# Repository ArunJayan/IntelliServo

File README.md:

IntelliServo
===================================================================

##Overview
IntelliServo is a project aiming to transform regular hobby servos into intelligent ones by replacing their original boards. 
By doing so the servo has upgraded capabilities, such as being able to read its position, temperature and current consumption. 
Multiple servos can now be daisy-chained and controlled over I2C from a microcontroller, or over USB from a computer.

Each board features an LPC11U24 microcontroller, a DRV8837 motor driver, a TMP36 temperature sensor and a PCA9508 I2C repeater.
Each servo is unique, and so the list of compatible servos will expand with the community, so don't hesitate to add your servo!

<div style="width: 100%; display: table;">
<div style="display: table-row">

<div align="center" style="display: table-cell;"><p align="center"><a href="https://youtu.be/W2uScJmLD4c" target="_blank">Master/Slave configuration</a></p></div>

<div align="center" style="display: table-cell;">
<p align="center"><a href="https://youtu.be/FjYgxcrhwy4" target="_blank">Touch detection</a></p>
</div>

</div>
</div>

##Connections
V_BAT: Main power line, energizes the motor and all the servo's ICs. Works between 5 and 12 volts.
V_I2C: Voltage reference for the I2C bus and powers components on the auxiliary bus. Must be 3.3V or 5V.

The servo has different connector groups:
* Main bus (5 lines): It is used to power and control the servos in daisy-chain configuration, attaching each one's A side to the previous' B side.
* Auxiliary bus (4 lines): Its function is to provide an extra link to the I2C bus, to allow other devices to be used at the same time.
* Power bus (2 lines): The main bus can be powered from the power bus on any servo, or from the last servo's main bus V_BAT and GND.
* Micro USB: Used both to upload the firmware to the board as to use it to control the servo directly from the PC, without involving other microcontrollers.

##Installing Firmware
The board runs the firmware included in the Software/Firmware section. It is written in C++ and uses Mbed, to upload it connect the board over USB and then power it using the V_BAT and GND lines while pressing the button. 

To compile it use the "mBuino" Mbed platform, which uses the smaller LPC11U24FHI33/301 model instead of the larger LPC11U24FBD64/401 model normally used in other boards. This is important because the EEPROM memory maps are different between both and the board won't be able to access the EEPROM until the right platform is chosen.

##Library
The servos are controlled over I2C, but to simplify their use an arduino library with all the relevant functions and some example sketches are included as well. 
To install it simply copy it to the "sketchbook/libraries/" folder. 

##Specifications
V_BAT:&nbsp;&nbsp;&nbsp;&nbsp;&nbsp;5V-12V
V_I2C:&nbsp;&nbsp;&nbsp;&nbsp;&nbsp;&nbsp;&nbsp;3.3V/5V
I_Servo:&nbsp;&nbsp;&nbsp;&nbsp;1.8A max
I_Line:&nbsp;&nbsp;&nbsp;&nbsp;&nbsp;&nbsp;&nbsp;5A max (60mil trace)

##Contributing
This project is open-source and as so everyone is welcome to contribute. The most useful way of doing so is perhaps by expanding the list of compatible servos, by finding the moving range in degrees and PID parameters specific for each servo.

To do so add the servo to the IntelliServoConfig.h file as below

```cpp
//Added by username
#ifdef NAME_OF_SERVO
    float maxAngle=XXX;
    float Kp=XXX, Kd=XXX, Ki=XXX;
#endif
```
and to the IntelliServoMain.cpp file
```cpp
//#define NAME_OF_SERVO
```

##License
This project is licensed under Creative Commons Attribution-ShareAlike 4.0 International (CC BY-SA 4.0)

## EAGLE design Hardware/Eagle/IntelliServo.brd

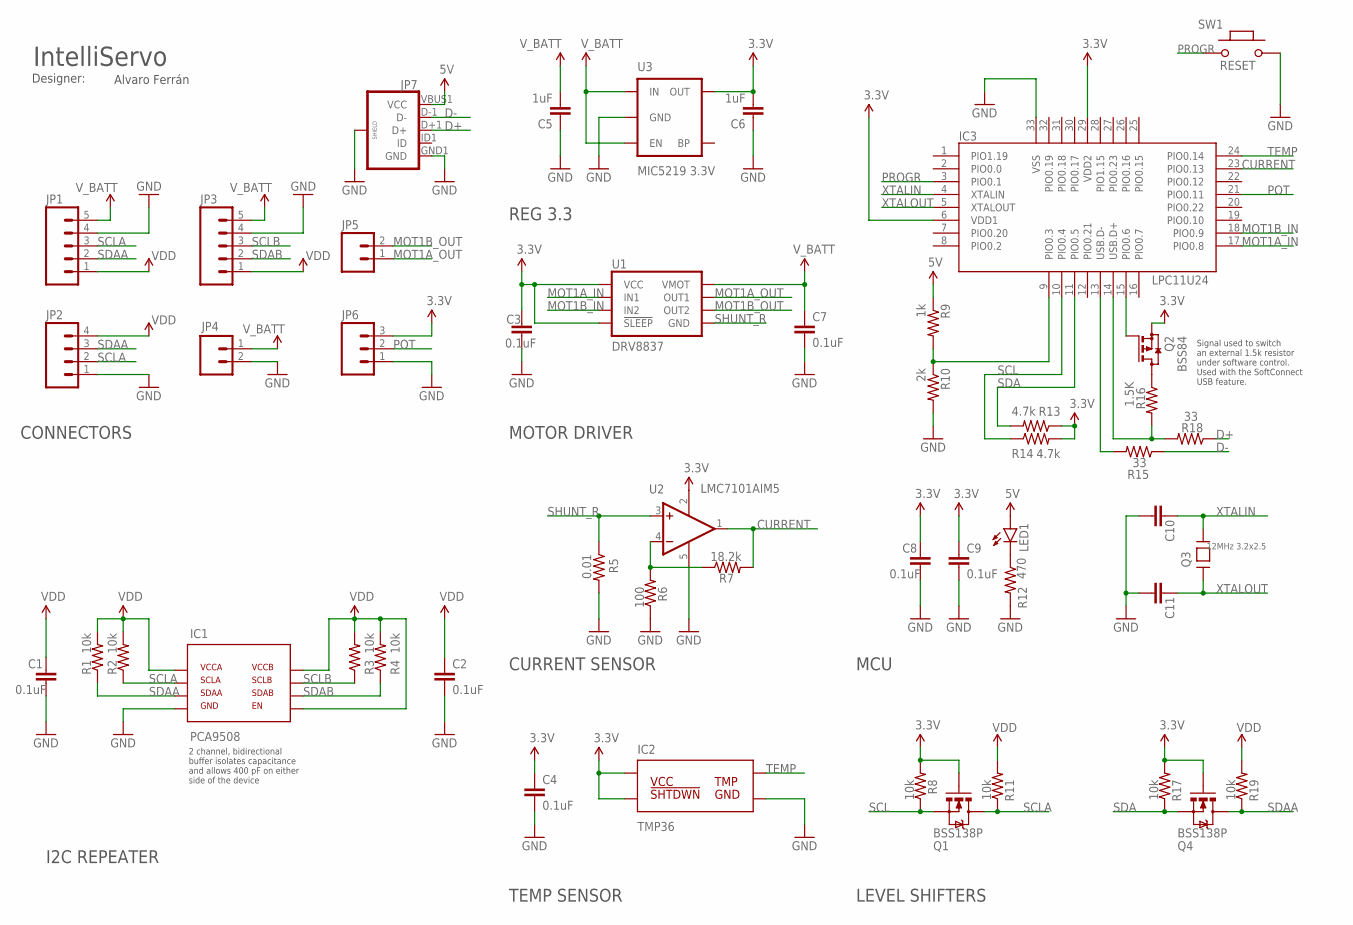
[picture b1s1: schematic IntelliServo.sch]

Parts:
C1, C2, C3, C4, C7, C8, C9: 0.1uF; 0402-CAP
C5, C6: 1uF; 0402-CAP
C10, C11: 27pF; 0402-CAP
IC1: PCA9508; TSSOP8
IC2: TMP36; SOT23-5
IC3: LPC11U24; HVQFN33_5X5MM
JP1, JP3: M05LOCK; 1X05_LOCK
JP2: M04LOCK; 1X04_LOCK
JP4, JP5: M02LOCK; 1X02_LOCK
JP6: M03LOCK; 1X03_LOCK
JP7: USB_MICROB; USB-B-MICRO-SMD_V03
LED1: LED0603; LED-0603
Q1, Q4: BSS138P; SOT23-3
Q2: BSS84; SOT23
Q3: 12MHz 3.2x2.5; CRYSTAL_3.2X2.5
R1, R2, R3, R4, R8, R11, R17, R19: 10k; 0402-RES
R5: 0.01; 0805
R6: 100; 0402-RES
R7: 18.2k; 0402-RES
R9: 1k; 0402-RES
R10: 2k; 0402-RES
R12: 470; 0402-RES
R13, R14: 4.7k; 0402-RES
R15, R18: 33; 0402-RES
R16: 1.5K; 0402-RES
SW1: RESET; 157SW
U1: DRV8837; DSG
U2: LMC7101AIM5; SOT23-5
U3: MIC5219 3.3V; SOT23-5

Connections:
3.3V: C3.1, C4.1, C6.2, C8.1, C9.1, IC2.2 (VCC), IC2.4 (!SHTDWN), IC3.6 (VDD1), IC3.29 (VDD2), JP6.3, Q1.1 (G), Q2.2 (S), Q4.1 (G), R8.2, R13.1, R14.2, R17.2, U1.7 (!SLEEP), U1.8 (VCC), U2.2 (V+), U3.5 (OUT)
5V: JP7.VBUS1 (VCC), LED1.A, R9.1
CURRENT: IC3.23 (PIO0.13), R7.2, U2.1 (OUT)
D+: JP7.D+1 (D+), R18.1
D-: JP7.D-1 (D-), R15.1
GND: C1.2, C2.2, C3.2, C4.2, C5.1, C6.1, C7.2, C8.2, C9.2, C10.2, C11.2, IC1.4 (GND), IC2.5 (GND), IC3.33 (VSS), JP1.4, JP2.1, JP3.4, JP4.2, JP6.1, JP7.GND1 (GND), JP7.SHIELD1 (SHIELD), JP7.SHIELD2 (SHIELD), JP7.SHIELD3 (SHIELD), R5.2, R6.1, R10.2, R12.2, SW1.2, U2.5 (V-), U3.2 (GND)
MOT1A_IN: IC3.17 (PIO0.8), U1.6 (IN1)
MOT1A_OUT: JP5.1, U1.2 (OUT1)
MOT1B_IN: IC3.18 (PIO0.9), U1.5 (IN2)
MOT1B_OUT: JP5.2, U1.3 (OUT2)
unnamed: LED1.C, R12.1
unnamed: R6.2, R7.1, U2.4 (-IN)
unnamed: IC3.14 (USB.D+), R16.2, R18.2
unnamed: IC3.13 (USB.D-), R15.2
unnamed: Q2.3 (D), R16.1
unnamed: IC3.15 (PIO0.6), Q2.1 (G)
P0.3/ISP_COMMAND_USB_HIGH: IC3.9 (PIO0.3), R9.2, R10.1
POT: IC3.21 (PIO0.11), JP6.2
PROGR: IC3.3 (PIO0.1), SW1.1
SCL: IC3.10 (PIO0.4), Q1.2 (S), R8.1, R14.1
SCLA: IC1.2 (SCLA), JP1.3, JP2.2, Q1.3 (D), R2.1, R11.1
SCLB: IC1.7 (SCLB), JP3.3, R3.1
SDA: IC3.11 (PIO0.5), Q4.2 (S), R13.2, R17.1
SDAA: IC1.3 (SDAA), JP1.2, JP2.3, Q4.3 (D), R1.1, R19.1
SDAB: IC1.6 (SDAB), JP3.2, R4.1
SHUNT_R: R5.1, U1.4 (GND), U1.PAD (GND), U2.3 (+IN)
TEMP: IC2.1 (TMP), IC3.24 (PIO0.14)
VDD: C1.1, C2.1, IC1.1 (VCCA), IC1.5 (EN), IC1.8 (VCCB), JP1.1, JP2.4, JP3.1, R1.2, R2.2, R3.2, R4.2, R11.2, R19.2
V_BATT: C5.2, C7.1, JP1.5, JP3.5, JP4.1, U1.1 (VMOT), U3.1 (IN), U3.3 (EN)
XTALIN: C10.1, IC3.4 (XTALIN), Q3.3
XTALOUT: C11.1, IC3.5 (XTALOUT), Q3.1

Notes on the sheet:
Designer:
Alvaro Ferrán
IntelliServo
REG 3.3
MCU
MOTOR DRIVER
Signal used to switch an external 1.5k resistor under software control. Used with the SoftConnect USB feature.
CURRENT SENSOR
TEMP SENSOR
CONNECTORS
LEVEL SHIFTERS
I2C REPEATER
2 channel, bidirectional buffer isolates capacitance and allows 400 pF on either side of the device
PCA9508
IC2
TMP36
IC1

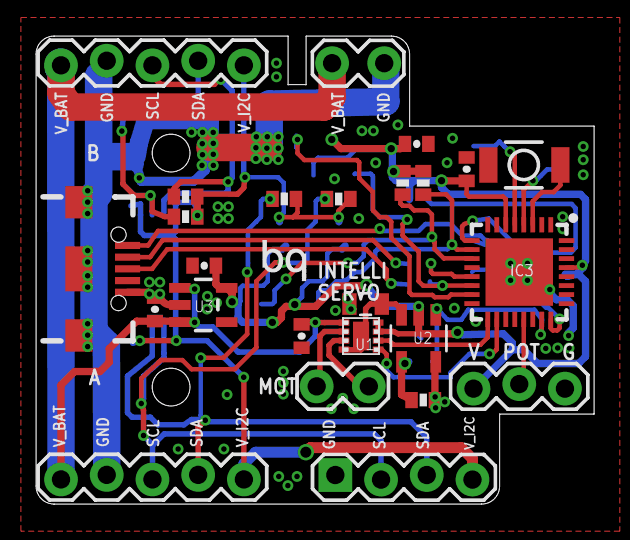
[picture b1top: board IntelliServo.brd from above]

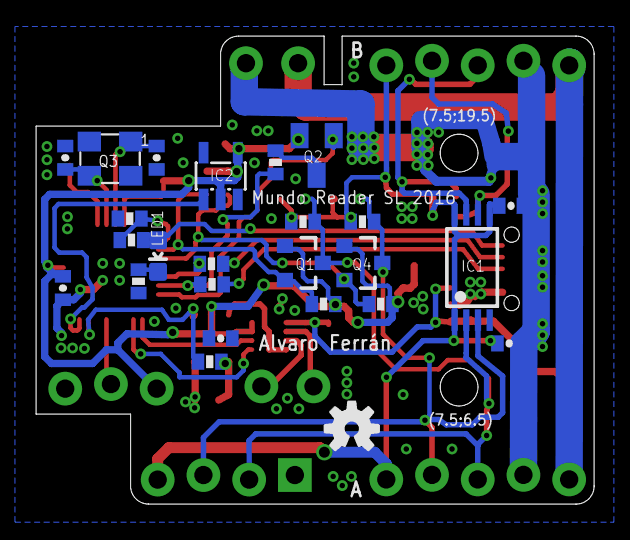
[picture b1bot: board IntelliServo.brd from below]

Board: 2 copper layers, 31.0 x 26.0 mm, 51 parts (25 on the bottom side), 31 nets.

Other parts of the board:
U$1: BQ_LOGO_SMALL_1
U$2: OSHW-LOGO-S

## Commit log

2016-03-09 Project added
2016-03-09 Create gh-pages branch via GitHub
2016-03-09 Interactive added
2016-03-14 json added

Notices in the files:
parts and their libraries:
SparkFun-Passives: Licensing: Creative Commons ShareAlike 4.0 International - https://creativecommons.org/licenses/by-sa/4.0
